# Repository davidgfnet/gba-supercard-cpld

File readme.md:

# GBA Supercard CPLD disassembly

CUPL-like equations for each macrocell can be found in the [report file](https://html-preview.github.io/?url=https://github.com/davidgfnet/gba-supercard-cpld/blob/master/report.html).

It would likely be much more understandable if readable signal/macrocell names were added based on which pins are hooked up to the GBA expansion bus and the various memory ICs.  There are comments in [main.zig](./main.zig) explaining how to specify these.  Afterwards, the report can be regenerated by running `zig build` from the repo directory.  This will require [Zig 0.14](https://ziglang.org/download/#release-0.14.0).

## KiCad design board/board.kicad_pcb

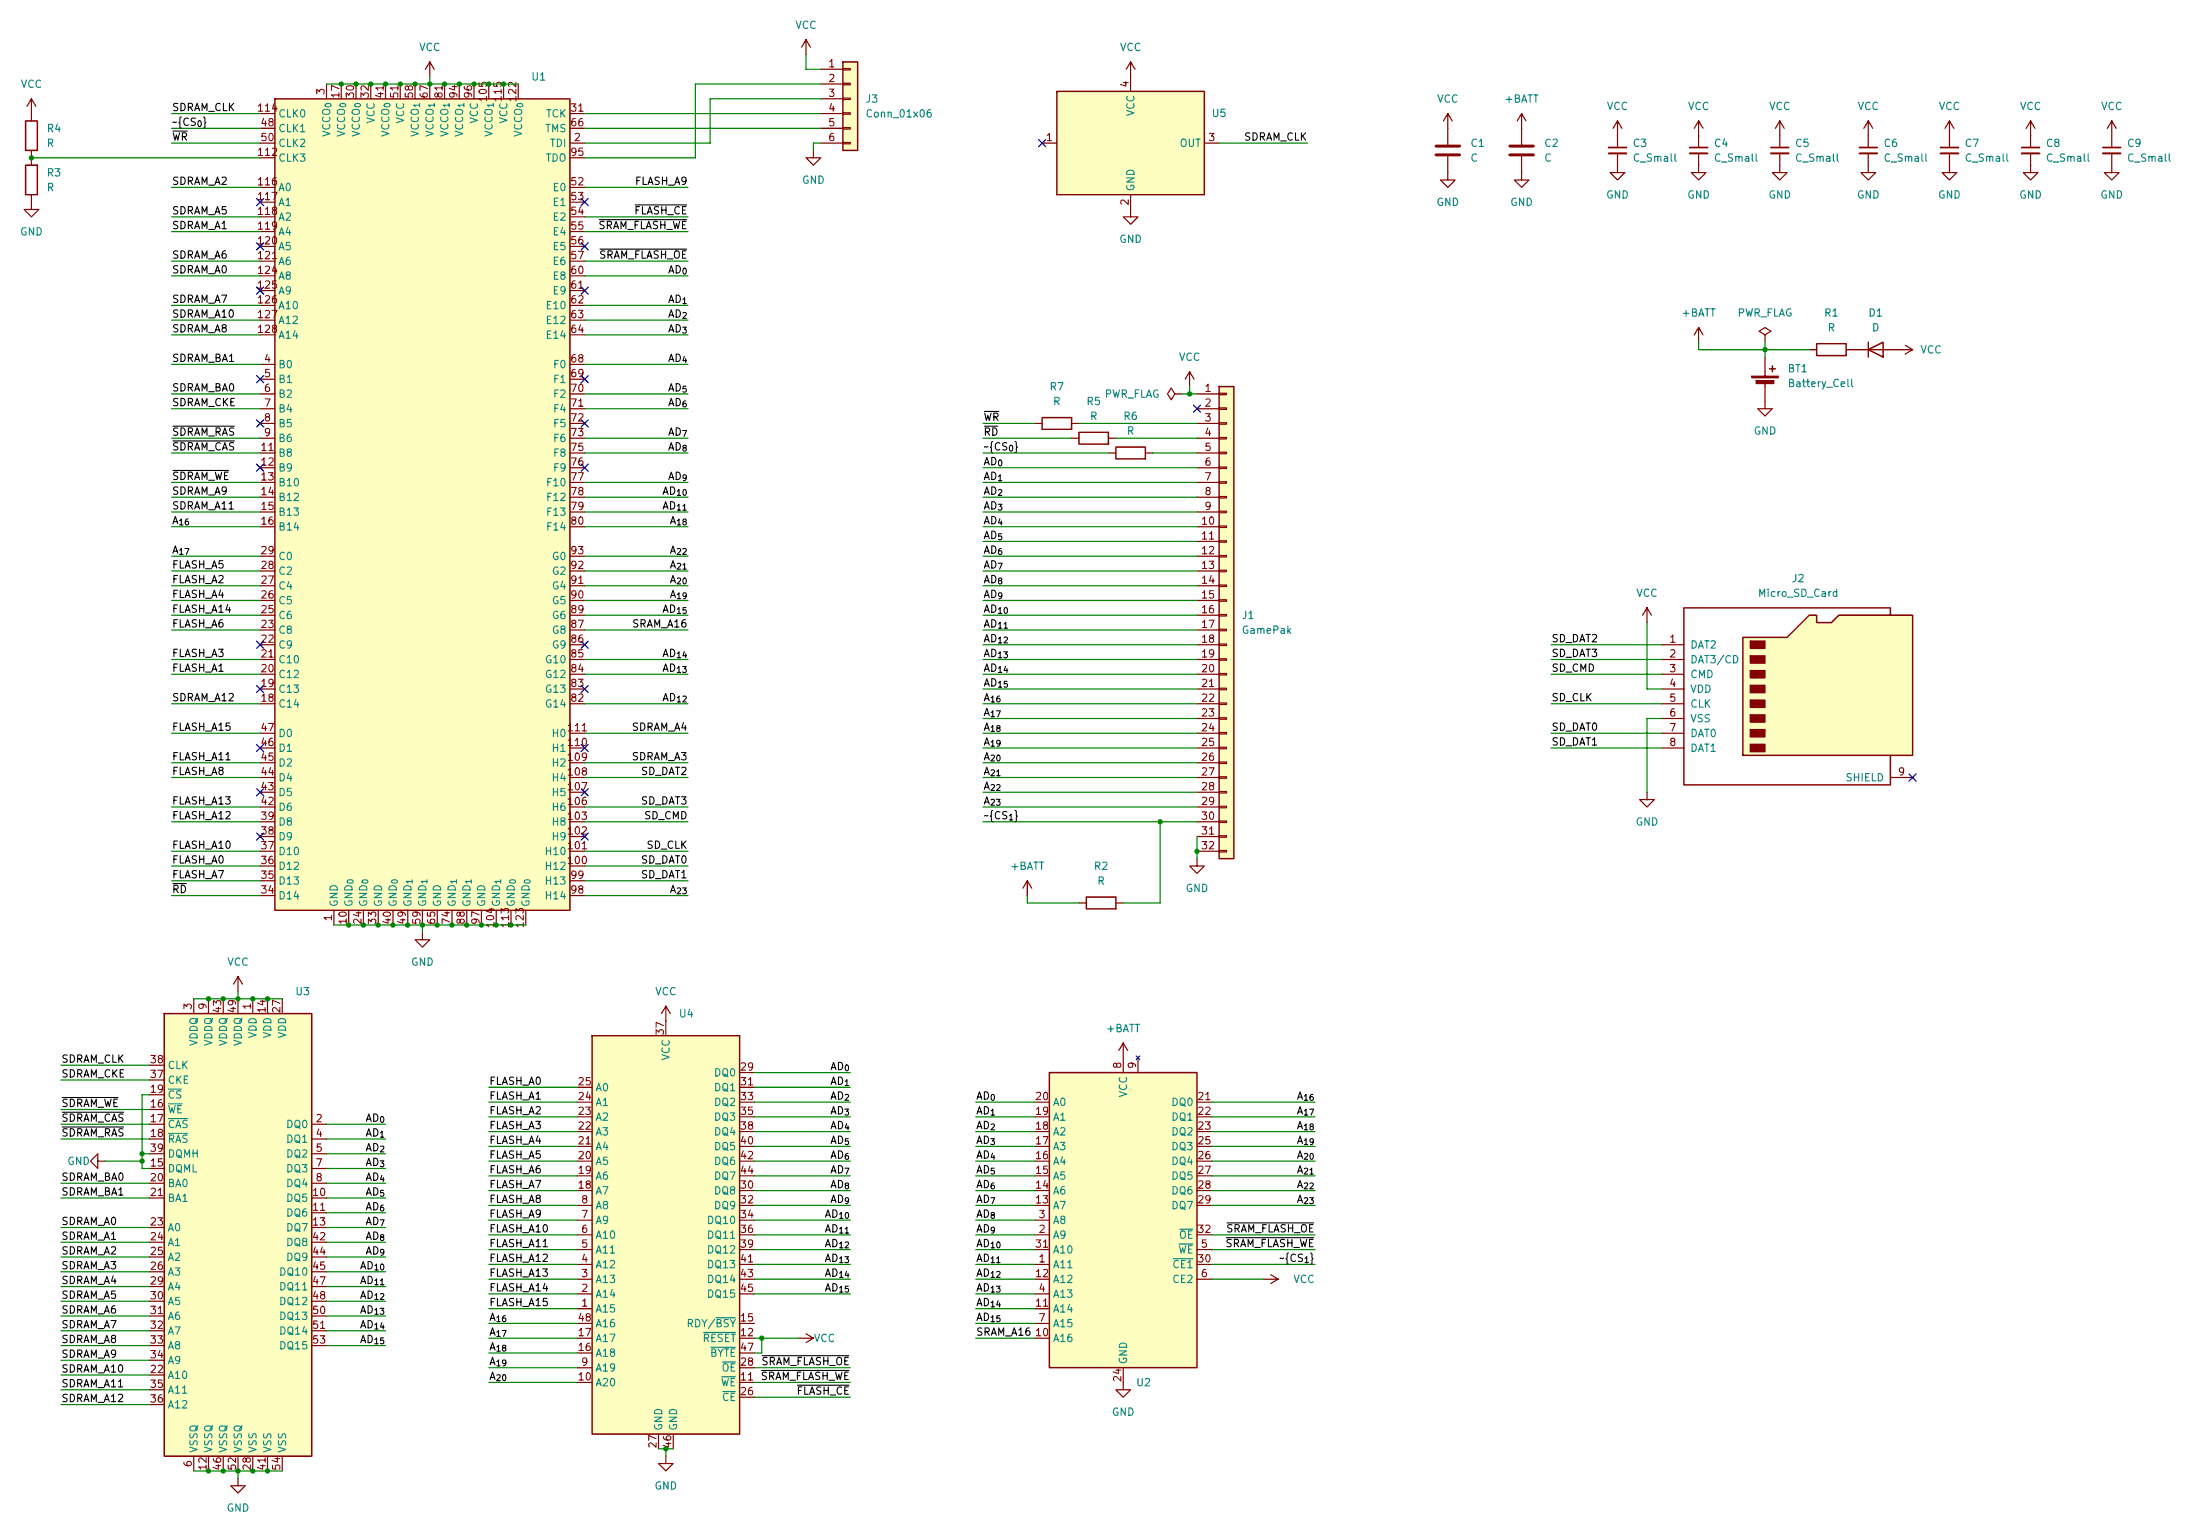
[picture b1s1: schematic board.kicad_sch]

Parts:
BT1: Battery_Cell; Battery
C1, C2: C; C_1206_3216Metric
C3, C4, C5, C6, C7, C8, C9: C_Small; C_0402_1005Metric
D1: D; D_SOD-323_HandSoldering
J1: GamePak; GamePak_CardEdge
J2: Micro_SD_Card; J_SD_Card-micro_socket_A
J3: Conn_01x06; JTAG
R1, R2, R3, R4, R5, R6, R7: R; R_0603_1608Metric
U1: TQFP-128_14x14mm_P0.4mm
U2: TSOP-I-32_11.8x8mm_P0.5mm
U3: TSOP-II-54_22.2x10.16mm_P0.8mm
U4: TSOP-I-48_18.4x12mm_P0.5mm
U5: Oscillator

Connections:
+BATT: BT1.1 (+), C2.1, R1.1, R2.1, U2.8 (VCC)
/AD_{0}: J1.6, U1.60 (E8), U2.20 (A0), U3.2 (DQ0), U4.29 (DQ0)
/AD_{1}: J1.7, U1.62 (E10), U2.19 (A1), U3.4 (DQ1), U4.31 (DQ1)
/AD_{2}: J1.8, U1.63 (E12), U2.18 (A2), U3.5 (DQ2), U4.33 (DQ2)
/AD_{3}: J1.9, U1.64 (E14), U2.17 (A3), U3.7 (DQ3), U4.35 (DQ3)
/AD_{4}: J1.10, U1.68 (F0), U2.16 (A4), U3.8 (DQ4), U4.38 (DQ4)
/AD_{5}: J1.11, U1.70 (F2), U2.15 (A5), U3.10 (DQ5), U4.40 (DQ5)
/AD_{6}: J1.12, U1.71 (F4), U2.14 (A6), U3.11 (DQ6), U4.42 (DQ6)
/AD_{7}: J1.13, U1.73 (F6), U2.13 (A7), U3.13 (DQ7), U4.44 (DQ7)
/AD_{8}: J1.14, U1.75 (F8), U2.3 (A8), U3.42 (DQ8), U4.30 (DQ8)
/AD_{9}: J1.15, U1.77 (F10), U2.2 (A9), U3.44 (DQ9), U4.32 (DQ9)
/AD_{10}: J1.16, U1.78 (F12), U2.31 (A10), U3.45 (DQ10), U4.34 (DQ10)
/AD_{11}: J1.17, U1.79 (F13), U2.1 (A11), U3.47 (DQ11), U4.36 (DQ11)
/AD_{12}: J1.18, U1.82 (G14), U2.12 (A12), U3.48 (DQ12), U4.39 (DQ12)
/AD_{13}: J1.19, U1.84 (G12), U2.4 (A13), U3.50 (DQ13), U4.41 (DQ13)
/AD_{14}: J1.20, U1.85 (G10), U2.11 (A14), U3.51 (DQ14), U4.43 (DQ14)
/AD_{15}: J1.21, U1.89 (G6), U2.7 (A15), U3.53 (DQ15), U4.45 (DQ15)
/A_{16}: J1.22, U1.16 (B14), U2.21 (DQ0), U4.48 (A16)
/A_{17}: J1.23, U1.29 (C0), U2.22 (DQ1), U4.17 (A17)
/A_{18}: J1.24, U1.80 (F14), U2.23 (DQ2), U4.16 (A18)
/A_{19}: J1.25, U1.90 (G5), U2.25 (DQ3), U4.9 (A19)
/A_{20}: J1.26, U1.91 (G4), U2.26 (DQ4), U4.10 (A20)
/A_{21}: J1.27, U1.92 (G2), U2.27 (DQ5)
/A_{22}: J1.28, U1.93 (G0), U2.28 (DQ6)
/A_{23}: J1.29, U1.98 (H14), U2.29 (DQ7)
/FLASH_A0: U1.36 (D12), U4.25 (A0)
/FLASH_A1: U1.20 (C12), U4.24 (A1)
/FLASH_A2: U1.27 (C4), U4.23 (A2)
/FLASH_A3: U1.21 (C10), U4.22 (A3)
/FLASH_A4: U1.26 (C5), U4.21 (A4)
/FLASH_A5: U1.28 (C2), U4.20 (A5)
/FLASH_A6: U1.23 (C8), U4.19 (A6)
/FLASH_A7: U1.35 (D13), U4.18 (A7)
/FLASH_A8: U1.44 (D4), U4.8 (A8)
/FLASH_A9: U1.52 (E0), U4.7 (A9)
/FLASH_A10: U1.37 (D10), U4.6 (A10)
/FLASH_A11: U1.45 (D2), U4.5 (A11)
/FLASH_A12: U1.39 (D8), U4.4 (A12)
/FLASH_A13: U1.42 (D6), U4.3 (A13)
/FLASH_A14: U1.25 (C6), U4.2 (A14)
/FLASH_A15: U1.47 (D0), U4.1 (A15)
/SDRAM_A0: U1.124 (A8), U3.23 (A0)
/SDRAM_A1: U1.119 (A4), U3.24 (A1)
/SDRAM_A2: U1.116 (A0), U3.25 (A2)
/SDRAM_A3: U1.109 (H2), U3.26 (A3)
/SDRAM_A4: U1.111 (H0), U3.29 (A4)
/SDRAM_A5: U1.118 (A2), U3.30 (A5)
/SDRAM_A6: U1.121 (A6), U3.31 (A6)
/SDRAM_A7: U1.126 (A10), U3.32 (A7)
/SDRAM_A8: U1.128 (A14), U3.33 (A8)
/SDRAM_A9: U1.14 (B12), U3.34 (A9)
/SDRAM_A10: U1.127 (A12), U3.22 (A10)
/SDRAM_A11: U1.15 (B13), U3.35 (A11)
/SDRAM_A12: U1.18 (C14), U3.36 (A12)
/SDRAM_BA0: U1.6 (B2), U3.20 (BA0)
/SDRAM_BA1: U1.4 (B0), U3.21 (BA1)
/SDRAM_CKE: U1.7 (B4), U3.37 (CKE)
/SDRAM_CLK: U1.114 (CLK0), U3.38 (CLK), U5.3 (OUT)
/SD_CLK: J2.5 (CLK), U1.101 (H10)
/SD_CMD: J2.3 (CMD), U1.103 (H8)
/SD_DAT0: J2.7 (DAT0), U1.100 (H12)
/SD_DAT1: J2.8 (DAT1), U1.99 (H13)
/SD_DAT2: J2.1 (DAT2), U1.108 (H4)
/SD_DAT3: J2.2 (DAT3/CD), U1.106 (H6)
/SRAM_A16: U1.87 (G8), U2.10 (A16)
/~CS_{0}: R6.1, U1.48 (CLK1)
/~CS_{1}: J1.30, R2.2, U2.30 (~CE1)
/~FLASH_CE: U1.54 (E2), U4.26 (~CE)
/~RD: R5.1, U1.34 (D14)
/~SDRAM_CAS: U1.11 (B8), U3.17 (~CAS)
/~SDRAM_RAS: U1.9 (B6), U3.18 (~RAS)
/~SDRAM_WE: U1.13 (B10), U3.16 (~WE)
/~SRAM_FLASH_OE: U1.57 (E6), U2.32 (~OE), U4.28 (~OE)
/~SRAM_FLASH_WE: U1.55 (E4), U2.5 (~WE), U4.11 (~WE)
/~WR: R7.1, U1.50 (CLK2)
GND: BT1.2 (-), C1.2, C2.2, C3.2, C4.2, C5.2, C6.2, C7.2, C8.2, C9.2, J1.31, J1.32, J2.6 (VSS), J3.6, R3.1, U1.1 (GND), U1.10 (GND_{0}), U1.24 (GND_{0}), U1.33 (GND), U1.40 (GND_{0}), U1.49 (GND_{1}), U1.59 (GND_{1}), U1.65 (GND), U1.74 (GND_{1}), U1.88 (GND_{1}), U1.97 (GND), U1.104 (GND_{1}), U1.113 (GND_{0}), U1.123 (GND_{0}), U2.24 (GND), U3.6 (VSSQ), U3.12 (VSSQ), U3.15 (DQML), U3.19 (~CS), U3.28 (VSS), U3.39 (DQMH), U3.41 (VSS), U3.46 (VSSQ), U3.52 (VSSQ), U3.54 (VSS), U4.27 (GND), U4.46 (GND), U5.2 (GND)
unnamed: D1.1 (K), R1.2
unnamed: J1.3, R7.2
unnamed: J1.4, R5.2
unnamed: J1.5, R6.2
unnamed: J3.2, U1.95 (TDO)
unnamed: J3.3, U1.2 (TDI)
unnamed: J3.4, U1.31 (TCK)
unnamed: J3.5, U1.66 (TMS)
unnamed: R3.2, R4.2, U1.112 (CLK3)
VCC: C1.1, C3.1, C4.1, C5.1, C6.1, C7.1, C8.1, C9.1, D1.2 (A), J1.1, J2.4 (VDD), J3.1, R4.1, U1.3 (VCCO_{0}), U1.17 (VCCO_{0}), U1.30 (VCCO_{0}), U1.32 (VCC), U1.41 (VCCO_{0}), U1.51 (VCC), U1.58 (VCCO_{1}), U1.67 (VCCO_{1}), U1.81 (VCCO_{1}), U1.94 (VCCO_{1}), U1.96 (VCC), U1.105 (VCCO_{1}), U1.115 (VCC), U1.122 (VCCO_{0}), U2.6 (CE2), U3.1 (VDD), U3.3 (VDDQ), U3.9 (VDDQ), U3.14 (VDD), U3.27 (VDD), U3.43 (VDDQ), U3.49 (VDDQ), U4.12 (~RESET), U4.37 (VCC), U4.47 (~BYTE), U5.4 (VCC)

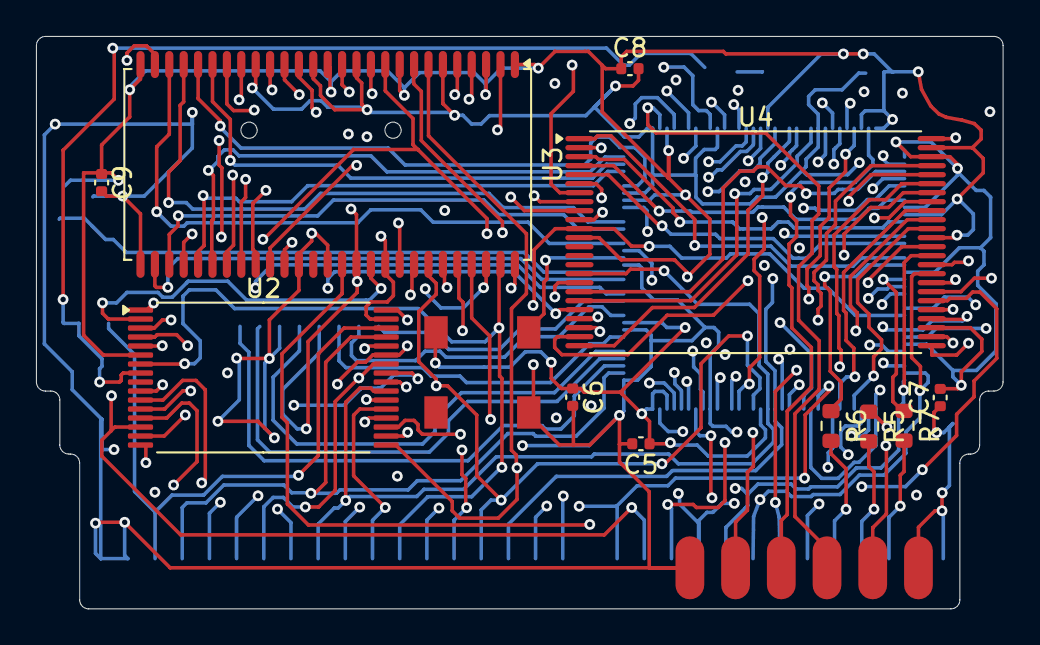
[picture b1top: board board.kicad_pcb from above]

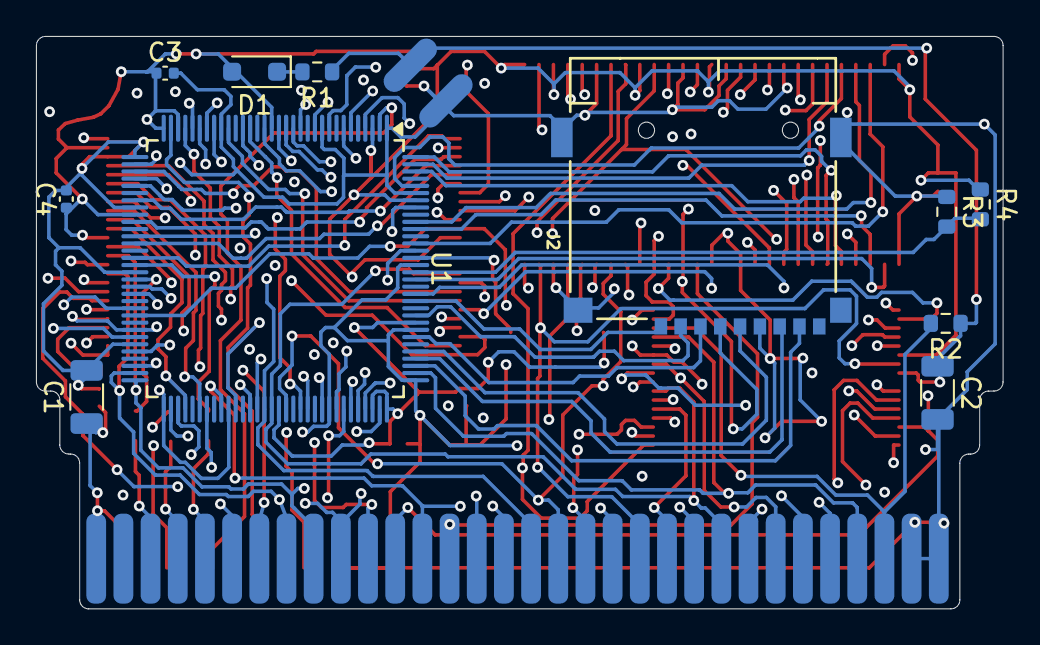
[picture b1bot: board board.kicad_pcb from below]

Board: 4 copper layers, 53.7 x 31.8 mm, 26 parts (13 on the bottom side), 86 nets.

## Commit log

2025-03-24 batman
2025-03-27 Adding more signals
2025-03-27 Controls & clocks
2025-03-27 Update signal names. Should cover them all.
2025-03-27 add kicad schematic/board
2025-03-27 Change package type (TQFP128)
2025-03-27 Testing out signal naming, seems to work fine. Need moar!
2025-03-27 A few more signals
2025-03-27 Fix signal numbering
2025-03-27 More signals
2025-03-27 Update report URI
2025-04-19 Name more signals too
2025-04-19 More signal naming
